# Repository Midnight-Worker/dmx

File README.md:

# dmx
com7 usb to rs485 dmx
com8 empfänger mit großem display
com9 sender mit kleinem display
com10 dmx
com11 esp32c6 i2c master

#set "PATH=C:\Program Files\Git\cmd;%USERPROFILE%\.platformio\penv\Scripts;C:\msys64\usr\bin;%PATH%"

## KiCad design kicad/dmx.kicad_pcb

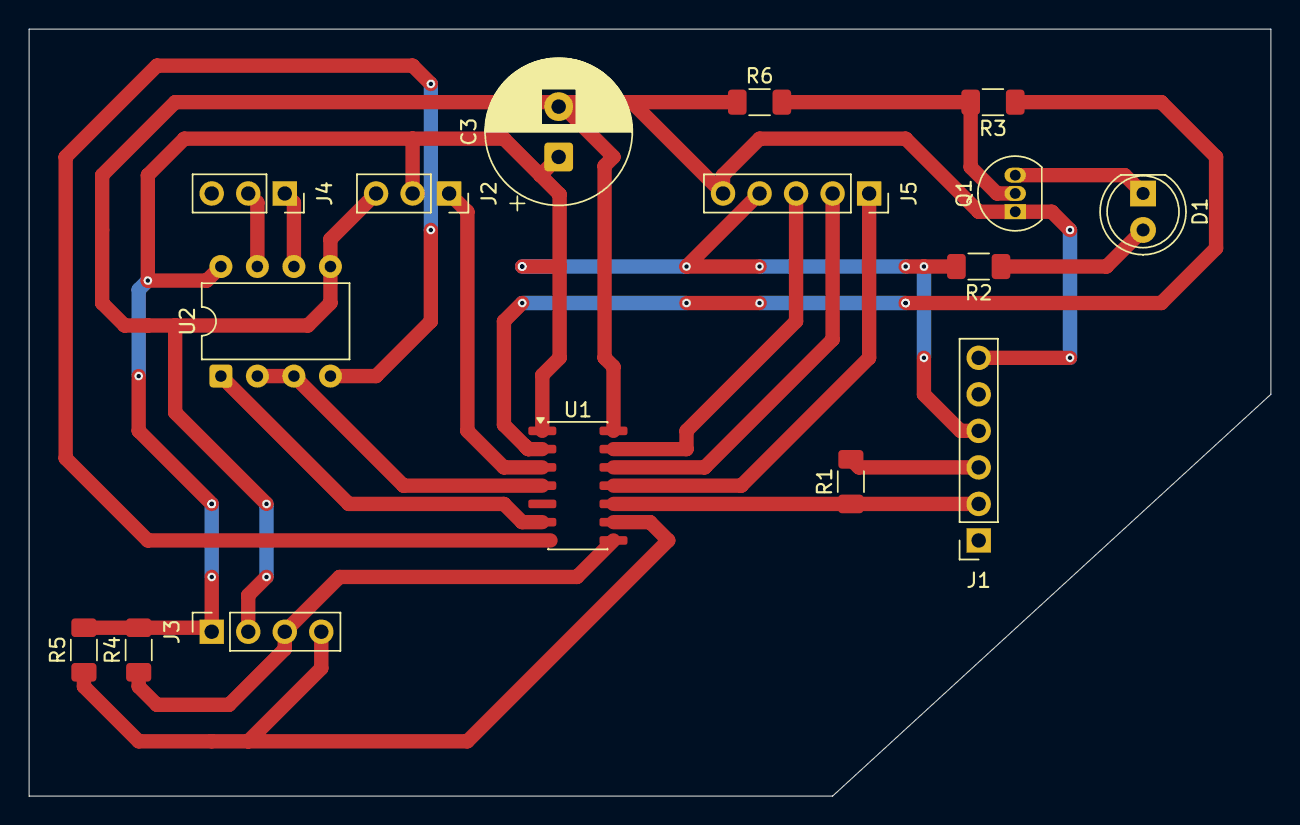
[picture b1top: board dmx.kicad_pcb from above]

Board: 2 copper layers, 86.4 x 53.3 mm, 16 parts (0 on the bottom side), 19 nets.

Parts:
C3: 10uF; CP_Radial_D10.0mm_P3.50mm
D1: Infrarotdiode; LED_D5.0mm_IRBlack
J1: Serieller Adapter USB; PinSocket_1x06_P2.54mm_Vertical
J2: Infrarot-Empfänger; PinSocket_1x03_P2.54mm_Vertical
J3: Display; PinSocket_1x04_P2.54mm_Vertical
J4: DMX; PinSocket_1x03_P2.54mm_Vertical
J5: Conn_01x05_Socket; PinSocket_1x05_P2.54mm_Vertical
Q1: PN2222A; TO-92_Inline
R1: R; R_1206_3216Metric_Pad1.30x1.75mm_HandSolder
R2: 47; R_1206_3216Metric_Pad1.30x1.75mm_HandSolder
R3: 1k; R_1206_3216Metric_Pad1.30x1.75mm_HandSolder
R4, R5: 4,7k; R_1206_3216Metric_Pad1.30x1.75mm_HandSolder
R6: 10k; R_1206_3216Metric_Pad1.30x1.75mm_HandSolder
U1: ATtiny814-SS; SOIC-14_3.9x8.7mm_P1.27mm
U2: MAX485E; DIP-8_W7.62mm

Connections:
+5V: C3.1, J1.4, J2.2, J3.1, J5.4, R2.2, R4.2, R5.2, U1.1 (VCC), U2.8 (VCC)
GND: C3.2, J1.6, J2.3, J3.2, J5.5, Q1.1 (E), R6.1, U1.14 (GND), U2.5 (GND)
unnamed: D1.2 (A), R2.1
unnamed: D1.1 (K), Q1.3 (C)
unnamed: J1.2, R1.1, U1.10 (~RESET/PA0)
unnamed: J1.3, R1.2
unnamed: J2.1, U1.3 (PA5)
unnamed: J3.3, R4.1, U1.8 (PB1)
unnamed: J3.4, R5.1, U1.9 (PB0)
unnamed: J4.1, U2.6 (A)
unnamed: J4.2, U2.7 (B)
unnamed: J5.1, U1.11 (PA1)
unnamed: J5.2, U1.12 (PA2)
unnamed: J5.3, U1.13 (PA3)
unnamed: Q1.2 (B), R3.2, R6.2
unnamed: R3.1, U1.2 (PA4)
unnamed: U1.4 (PA6), U2.2 (~RE), U2.3 (DE)
unnamed: U1.7 (PB2), U2.4 (DI)
unnamed: U1.6 (PB3), U2.1 (RO)
